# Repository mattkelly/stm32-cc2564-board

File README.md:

# STM32 + CC2564 Board

No idea what I'm doing

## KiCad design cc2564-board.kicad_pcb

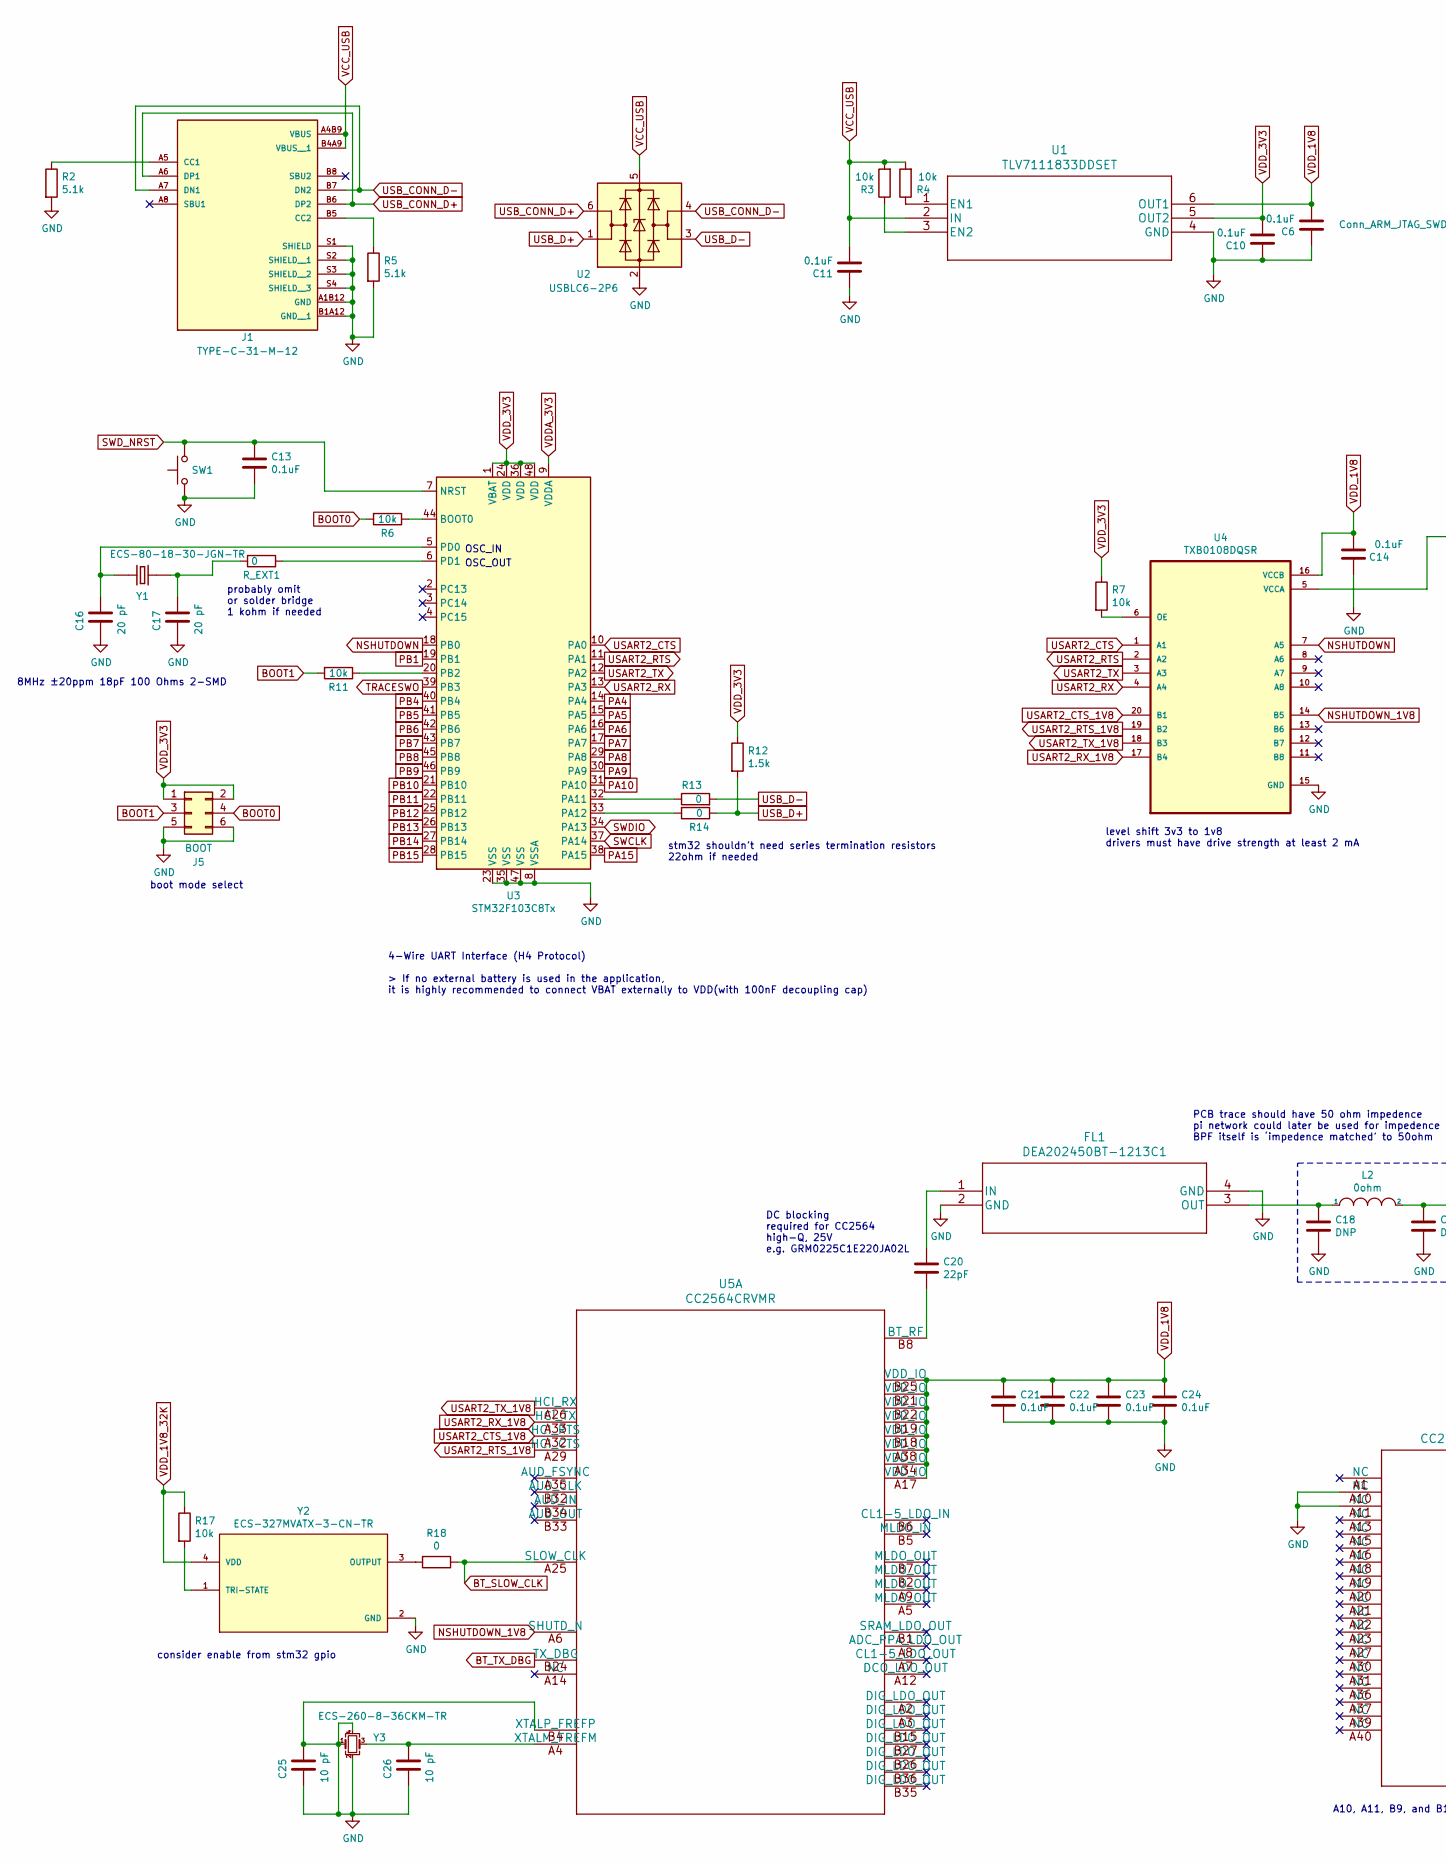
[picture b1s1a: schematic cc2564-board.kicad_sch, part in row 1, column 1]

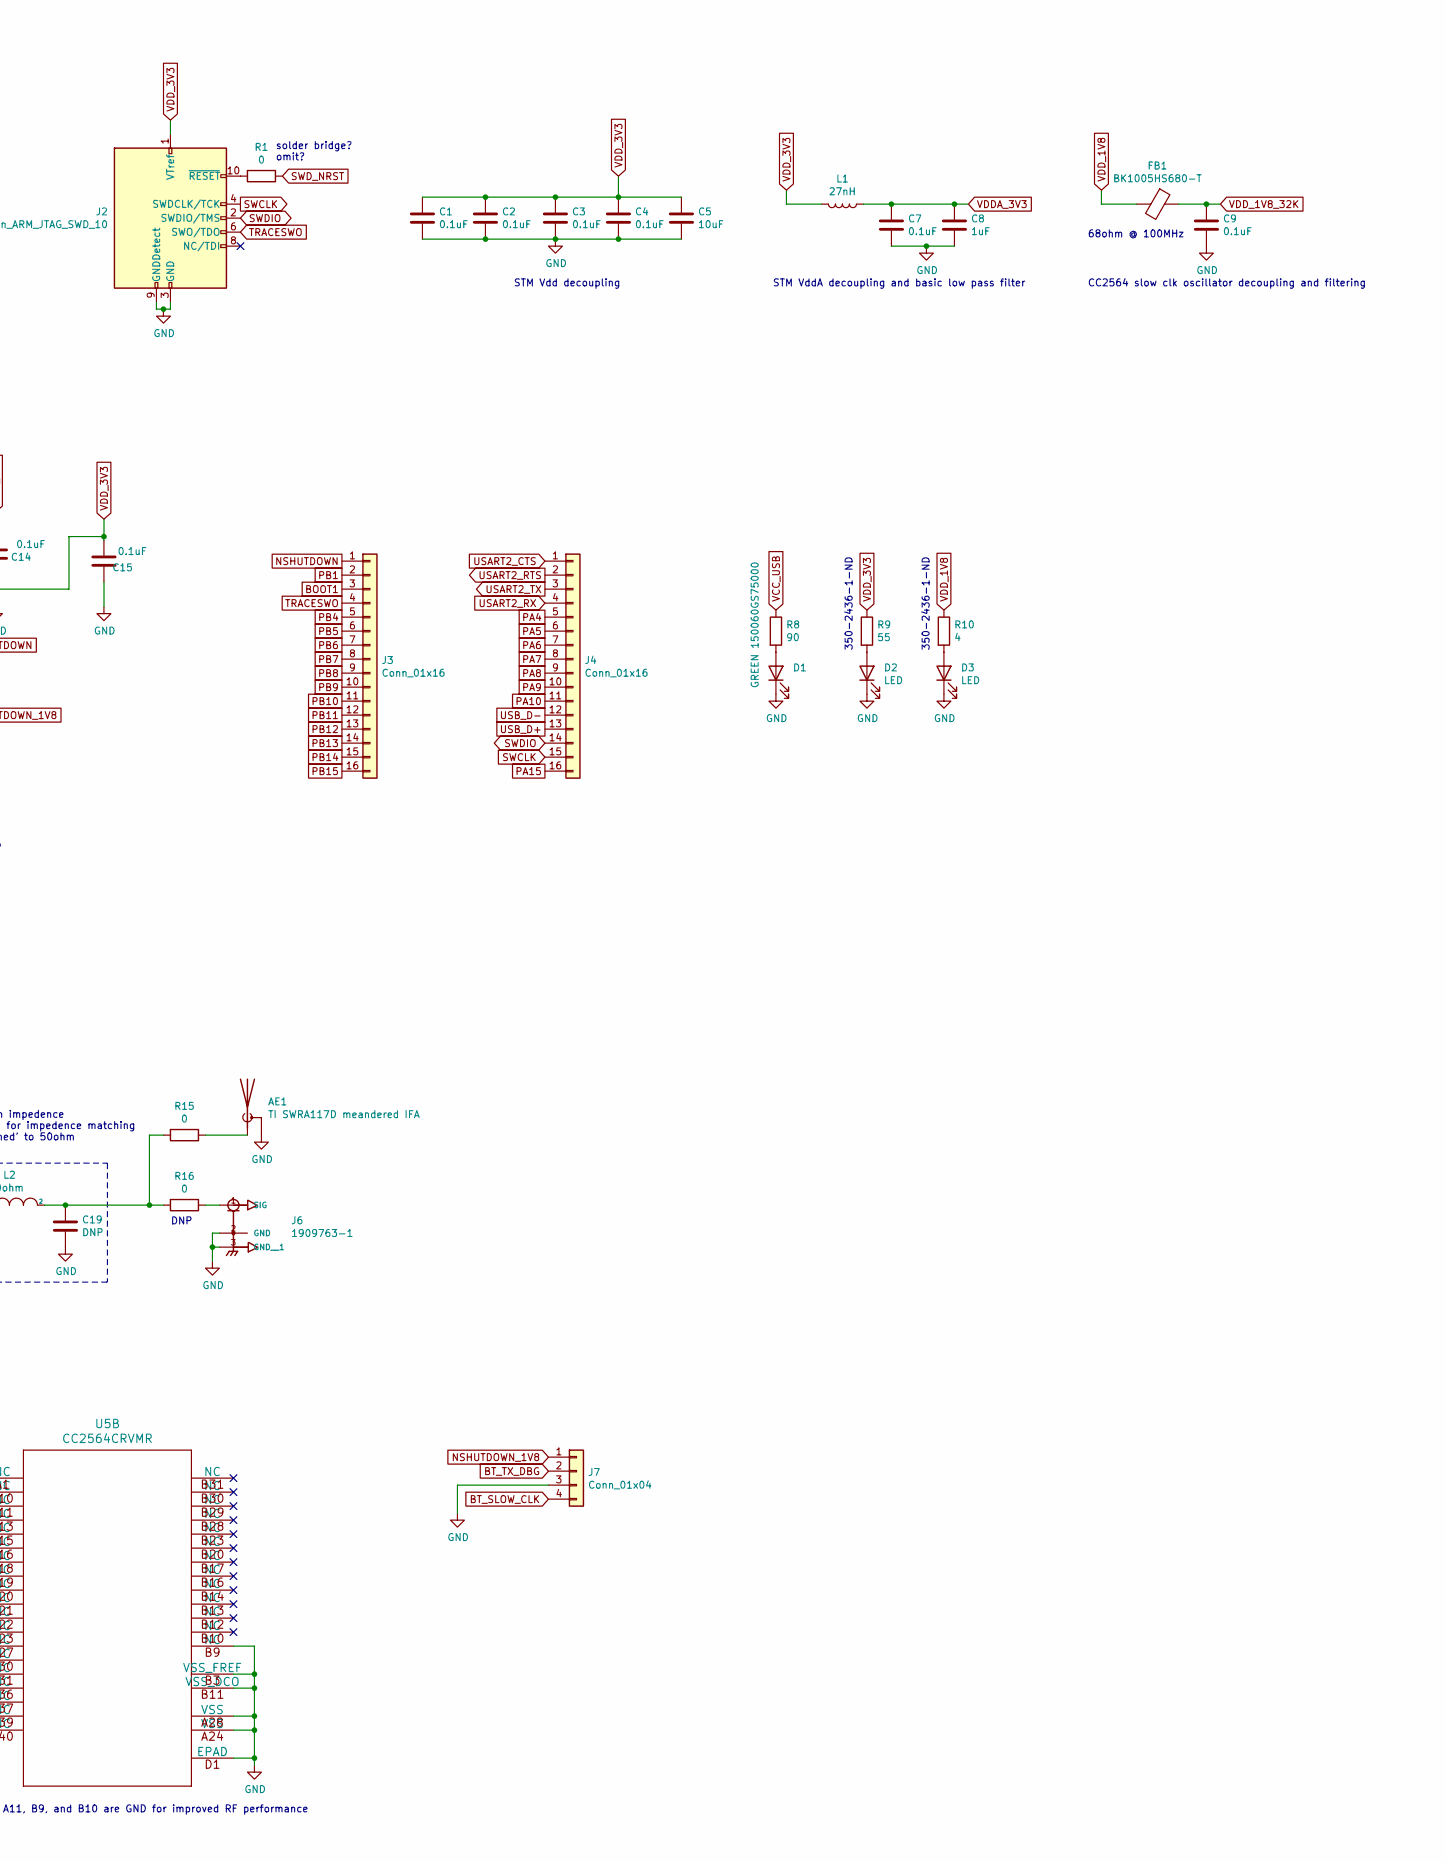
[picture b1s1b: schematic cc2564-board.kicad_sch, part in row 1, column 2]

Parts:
AE1: TI SWRA117D meandered IFA; Texas_SWRA117D_2.4GHz_Right
C1, C2, C3, C4, C6, C7, C9, C10, C11, C13, C14, C15, C21, C22, C23, C24: 0.1uF; C_0402_1005Metric_Pad0.74x0.62mm_HandSolder
C5: 10uF; C_0402_1005Metric_Pad0.74x0.62mm_HandSolder
C8: 1uF; C_0402_1005Metric_Pad0.74x0.62mm_HandSolder
C16, C17: 20 pF; C_0402_1005Metric_Pad0.74x0.62mm_HandSolder
C18, C19: DNP; C_0402_1005Metric_Pad0.74x0.62mm_HandSolder
C20: 22pF; C_0402_1005Metric_Pad0.74x0.62mm_HandSolder
C25, C26: 10 pF; C_0402_1005Metric_Pad0.74x0.62mm_HandSolder
D1: GREEN 150060GS75000; LED_0603_1608Metric_Pad1.05x0.95mm_HandSolder
D2, D3: LED; LED_0603_1608Metric_Pad1.05x0.95mm_HandSolder
FB1: BK1005HS680-T‎; L_0402_1005Metric_Pad0.77x0.64mm_HandSolder
FL1: DEA202450BT-1213C1
J1: TYPE-C-31-M-12; HRO_TYPE-C-31-M-12; PARTREV A
J2: Conn_ARM_JTAG_SWD_10; PinHeader_2x05_P1.27mm_Vertical
J3, J4: Conn_01x16; PinHeader_1x16_P1.27mm_Vertical
J5: BOOT; PinHeader_2x03_P1.27mm_Vertical
J6: 1909763-1; UFL-TE_1909763-1
J7: Conn_01x04; PinHeader_1x04_P1.27mm_Vertical
L1: 27nH; L_0402_1005Metric_Pad0.77x0.64mm_HandSolder
L2: 0ohm; L_0402_1005Metric_Pad0.77x0.64mm_HandSolder
R1, R13, R14, R15, R16, R18: 0; R_0402_1005Metric_Pad0.72x0.64mm_HandSolder
R2, R5: 5.1k; R_0402_1005Metric_Pad0.72x0.64mm_HandSolder
R3, R4, R6, R7, R11, R17: 10k; R_0402_1005Metric_Pad0.72x0.64mm_HandSolder
R8: 90; R_0402_1005Metric_Pad0.72x0.64mm_HandSolder
R9: 55; R_0402_1005Metric_Pad0.72x0.64mm_HandSolder
R10: 4; R_0402_1005Metric_Pad0.72x0.64mm_HandSolder
R12: 1.5k; R_0402_1005Metric_Pad0.72x0.64mm_HandSolder
R_EXT1: 0; R_0402_1005Metric_Pad0.72x0.64mm_HandSolder
SW1: SW_Push; TL3342F160QG_TR
U1: TLV7111833DDSET
U2: USBLC6-2P6; SOT-666
U3: STM32F103C8Tx; LQFP-48_7x7mm_P0.5mm
U4: TXB0108DQSR
U5: CC2564CRVMR
Y1: ECS-80-18-30-JGN-TR; XTAL_ECS-80-18-30-JGN-TR; PARTREV 2017
Y2: ECS-327MVATX-3-CN-TR; OSC_ECS-2333-160-BN-TR; PARTREV N/A
Y3: ECS-260-8-36CKM-TR; XTAL_ECS-260-8-36CKM-TR

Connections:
BOOT0: J5.4, R6.2
BOOT1: J3.3, J5.3, R11.2
BT_SLOW_CLK: J7.4, R18.1, U5.A25 (SLOW_CLK)
BT_TX_DBG: J7.2, U5.B24 (TX_DBG)
GND: AE1.2 (Shield), C1.2, C2.2, C3.2, C4.2, C5.2, C6.1, C7.2, C8.2, C9.2, C10.1, C11.1, C13.2, C14.1, C15.1, C16.1, C17.1, C18.2, C19.2, C21.2, C22.2, C23.2, C24.2, C25.1, C25.2, C26.1, D1.1 (K), D2.1 (K), D3.1 (K), FL1.2 (GND), FL1.4 (GND), J1.A1B12 (GND), J1.B1A12 (GND__1), J1.S1 (SHIELD), J1.S2 (SHIELD__1), J1.S3 (SHIELD__2), J1.S4 (SHIELD__3), J2.3 (GND), J2.5 (GND), J2.9 (GNDDetect), J5.5, J5.6, J6.2 (GND), J6.3 (GND__1), J7.3, R2.2, R5.2, SW1.1, U1.4 (GND), U2.2 (GND), U3.8 (VSSA), U3.23 (VSS), U3.35 (VSS), U3.47 (VSS), U4.15 (GND), U5.A10 (NC), U5.A11 (NC), U5.A24 (VSS), U5.A28 (VSS), U5.B3 (VSS_FREF), U5.B4 (XTALP_FREFP), U5.B9 (NC), U5.B11 (VSS_DCO), U5.D1 (EPAD), Y2.2 (GND), Y3.1, Y3.2, Y3.4
NSHUTDOWN: J3.1, U3.18 (PB0), U4.7 (A5)
NSHUTDOWN_1V8: J7.1, U4.14 (B5), U5.A6 (SHUTD_N)
unnamed: AE1.1 (A), R15.1
unnamed: C16.2, U3.5 (PD0), Y1.1
unnamed: C17.2, R_EXT1.2, Y1.2
unnamed: C18.1, FL1.3 (OUT), L2.1
unnamed: C19.1, L2.2, R15.2, R16.2
unnamed: C20.1, FL1.1 (IN)
unnamed: C20.2, U5.B8 (BT_RF)
unnamed: C26.2, U5.A4 (XTALM_FREFM), Y3.3
unnamed: D1.2 (A), R8.2
unnamed: D2.2 (A), R9.2
unnamed: D3.2 (A), R10.2
unnamed: J1.A5 (CC1), R2.1
unnamed: J1.B5 (CC2), R5.1
unnamed: J2.10 (~RESET~), R1.2
unnamed: J6.1 (SIG), R16.1
unnamed: R3.1, U1.3 (EN2)
unnamed: R4.1, U1.1 (EN1)
unnamed: R6.1, U3.44 (BOOT0)
unnamed: R7.2, U4.6 (OE)
unnamed: R11.1, U3.20 (PB2)
unnamed: R13.1, U3.32 (PA11)
unnamed: R14.2, U3.33 (PA12)
unnamed: R17.2, Y2.1 (TRI-STATE)
unnamed: R18.2, Y2.3 (OUTPUT)
unnamed: R_EXT1.1, U3.6 (PD1)
PA4: J4.5, U3.14 (PA4)
PA5: J4.6, U3.15 (PA5)
PA6: J4.7, U3.16 (PA6)
PA7: J4.8, U3.17 (PA7)
PA8: J4.9, U3.29 (PA8)
PA9: J4.10, U3.30 (PA9)
PA10: J4.11, U3.31 (PA10)
PA15: J4.16, U3.38 (PA15)
PB1: J3.2, U3.19 (PB1)
PB4: J3.5, U3.40 (PB4)
PB5: J3.6, U3.41 (PB5)
PB6: J3.7, U3.42 (PB6)
PB7: J3.8, U3.43 (PB7)
PB8: J3.9, U3.45 (PB8)
PB9: J3.10, U3.46 (PB9)
PB10: J3.11, U3.21 (PB10)
PB11: J3.12, U3.22 (PB11)
PB12: J3.13, U3.25 (PB12)
PB13: J3.14, U3.26 (PB13)
PB14: J3.15, U3.27 (PB14)
PB15: J3.16, U3.28 (PB15)
SWCLK: J2.4 (SWDCLK/TCK), J4.15, U3.37 (PA14)
SWDIO: J2.2 (SWDIO/TMS), J4.14, U3.34 (PA13)
SWD_NRST: C13.1, R1.1, SW1.2, U3.7 (NRST)
TRACESWO: J2.6 (SWO/TDO), J3.4, U3.39 (PB3)
USART2_CTS: J4.1, U3.10 (PA0), U4.1 (A1)
USART2_CTS_1V8: U4.20 (B1), U5.A32 (HCI_RTS)
USART2_RTS: J4.2, U3.11 (PA1), U4.2 (A2)
USART2_RTS_1V8: U4.19 (B2), U5.A29 (HCI_CTS)
USART2_RX: J4.4, U3.13 (PA3), U4.4 (A4)
USART2_RX_1V8: U4.17 (B4), U5.A33 (HCI_TX)
USART2_TX: J4.3, U3.12 (PA2), U4.3 (A3)
USART2_TX_1V8: U4.18 (B3), U5.A26 (HCI_RX)
USB_CONN_D+: J1.A6 (DP1), J1.B6 (DP2), U2.6 (I/O1)
USB_CONN_D-: J1.A7 (DN1), J1.B7 (DN2), U2.4 (I/O2)
USB_D+: J4.13, R12.2, R14.1, U2.1 (I/O1)
USB_D-: J4.12, R13.2, U2.3 (I/O2)
VCC_USB: C11.2, J1.A4B9 (VBUS), J1.B4A9 (VBUS__1), R3.2, R4.2, R8.1, U1.2 (IN), U2.5 (VBUS)
VDDA_3V3: C7.1, C8.1, L1.1, U3.9 (VDDA)
VDD_1V8: C6.2, C14.2, C21.1, C22.1, C23.1, C24.1, FB1.2, R10.1, U1.6 (OUT1), U4.16 (VCCB), U5.A17 (VDD_IO), U5.A34 (VDD_IO), U5.A38 (VDD_IO), U5.B18 (VDD_IO), U5.B19 (VDD_IO), U5.B21 (VDD_IO), U5.B22 (VDD_IO), U5.B25 (VDD_IO)
VDD_1V8_32K: C9.1, FB1.1, R17.1, Y2.4 (VDD)
VDD_3V3: C1.1, C2.1, C3.1, C4.1, C5.1, C10.2, C15.2, J2.1 (VTref), J5.1, J5.2, L1.2, R7.1, R9.1, R12.1, U1.5 (OUT2), U3.1 (VBAT), U3.24 (VDD), U3.36 (VDD), U3.48 (VDD), U4.5 (VCCA)
no_connect_76: J1.A8 (SBU1)
no_connect_77: J1.B8 (SBU2)
no_connect_78: J2.8 (NC/TDI)
no_connect_79: U3.2 (PC13)
no_connect_80: U3.3 (PC14)
no_connect_81: U3.4 (PC15)
no_connect_82: U4.10 (A8)
no_connect_83: U4.11 (B8)
no_connect_84: U4.12 (B7)
no_connect_85: U4.13 (B6)
no_connect_86: U4.8 (A6)
no_connect_87: U4.9 (A7)
no_connect_88: U5.A1 (NC)
no_connect_89: U5.A12 (DCO_LDO_OUT)
no_connect_90: U5.A13 (NC)
no_connect_91: U5.A14 (NC)
no_connect_92: U5.A15 (NC)
no_connect_93: U5.A16 (NC)
no_connect_94: U5.A18 (NC)
no_connect_95: U5.A19 (NC)
no_connect_96: U5.A2 (DIG_LDO_OUT)
no_connect_97: U5.A20 (NC)
no_connect_98: U5.A21 (NC)
no_connect_99: U5.A22 (NC)
no_connect_100: U5.A23 (NC)
no_connect_101: U5.A27 (NC)
no_connect_102: U5.A3 (DIG_LDO_OUT)
no_connect_103: U5.A30 (NC)
no_connect_104: U5.A31 (NC)
no_connect_105: U5.A35 (AUD_FSYNC)
no_connect_106: U5.A36 (NC)
no_connect_107: U5.A37 (NC)
no_connect_108: U5.A39 (NC)
no_connect_109: U5.A40 (NC)
no_connect_110: U5.A5 (MLDO_OUT)
no_connect_111: U5.A7 (CL1-5_LDO_OUT)
no_connect_112: U5.A8 (ADC_PPA_LDO_OUT)
no_connect_113: U5.A9 (MLDO_OUT)
no_connect_114: U5.B1 (SRAM_LDO_OUT)
no_connect_115: U5.B10 (NC)
no_connect_116: U5.B12 (NC)
no_connect_117: U5.B13 (NC)
no_connect_118: U5.B14 (NC)
no_connect_119: U5.B15 (DIG_LDO_OUT)
no_connect_120: U5.B16 (NC)
no_connect_121: U5.B17 (NC)
no_connect_122: U5.B2 (MLDO_OUT)
no_connect_123: U5.B20 (NC)
no_connect_124: U5.B23 (NC)
no_connect_125: U5.B26 (DIG_LDO_OUT)
no_connect_126: U5.B27 (DIG_LDO_OUT)
no_connect_127: U5.B28 (NC)
no_connect_128: U5.B29 (NC)
no_connect_129: U5.B30 (NC)
no_connect_130: U5.B31 (NC)
no_connect_131: U5.B32 (AUD_CLK)
no_connect_132: U5.B33 (AUD_OUT)
no_connect_133: U5.B34 (AUD_IN)
no_connect_134: U5.B35 (DIG_LDO_OUT)
no_connect_135: U5.B36 (DIG_LDO_OUT)
no_connect_136: U5.B5 (MLDO_IN)
no_connect_137: U5.B6 (CL1-5_LDO_IN)
no_connect_138: U5.B7 (MLDO_OUT)

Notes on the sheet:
8MHz ±20ppm 18pF 100 Ohms 2-SMD
boot mode select
consider enable from stm32 gpio
probably omit or solder bridge 1 kohm if needed
4-Wire UART Interface (H4 Protocol) > If no external battery is used in the application, it is highly recommended to connect VBAT externally to VDD(with 100nF decoupling cap)
OSC_IN
OSC_OUT
stm32 shouldn’t need series termination resistors 22ohm if needed
DC blocking required for CC2564 high-Q, 25V e.g. GRM0225C1E220JA02L
level shift 3v3 to 1v8 drivers must have drive strength at least 2 mA
PCB trace should have 50 ohm impedence pi network could later be used for impedence matching BPF itself is ‘impedence matched’ to 50ohm
A10, A11, B9, and B10 are GND for improved RF performance
DNP
solder bridge? omit?
STM Vdd decoupling
STM VddA decoupling and basic low pass filter
350-2436-1-ND‎
68ohm @ 100MHz
CC2564 slow clk oscillator decoupling and filtering

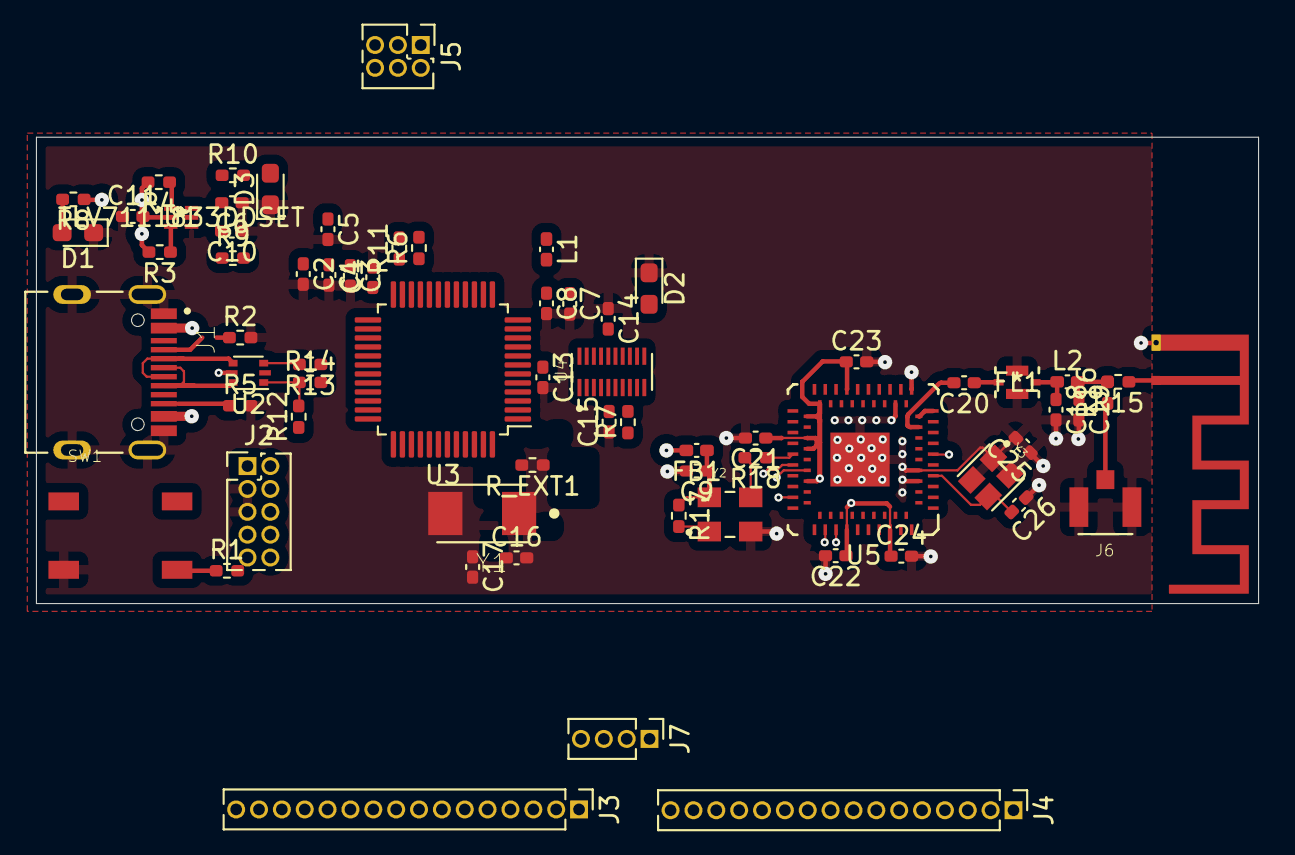
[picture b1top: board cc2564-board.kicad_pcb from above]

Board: 4 copper layers, 67.9 x 25.9 mm, 68 parts (0 on the bottom side), 74 nets.

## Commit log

2020-12-22 Forgot very important README
2020-12-23 Figure out STM32 crystal, hopefully
2020-12-23 Add magic TI level shifter
2020-12-23 Better CC2564 footprint, reorganize
2020-12-24 BT slow clock and other things I don't remember
2020-12-24 LEDs, maybe
2020-12-24 Decouple + filter VDDA
    Thanks https://www.youtube.com/watch?v=wLwKgMBWhpY
2020-12-26 Filter BT slow clock osc power input per datasheet
2020-12-26 Add USBLC6 for USB ESD protection
2020-12-26 Add UFL connector
2020-12-27 RF matching placeholder and filtering
2020-12-27 Remove extra 0ohm on SWD_NRST
2020-12-27 Fix up a bunch of footprints
2020-12-27 One header for boot mode
2020-12-27 Use meandered PIFA from TI app note AN043
2020-12-30 More footprint updates
2020-12-31 Specify high-Q DC blocking cap
2021-01-01 Switch to nightly, initial board setup, not exactly sure what to git add...
2021-01-01 Swap in TLV711 series 3v3/1v8 dual output LDO
    Thanks @noahp for inspiration
2021-01-02 Temp top ground fill, generally make a mess
2021-01-02 More board setup pain, route BT fast clock
2021-01-02 Swap out level shifters for one 8 channel QFN
2021-01-03 Begin serious layout
2021-01-09 Finish most BT stuff

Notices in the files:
parts and their libraries:
Copyright 2016 Accelerated Designs. All rights reserved.
